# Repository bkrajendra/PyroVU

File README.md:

# PyroVU - Universal temperature sensor interface board

PyroVU is an universal temperature sensor module interface board for Sonpakhru board

## User Interface

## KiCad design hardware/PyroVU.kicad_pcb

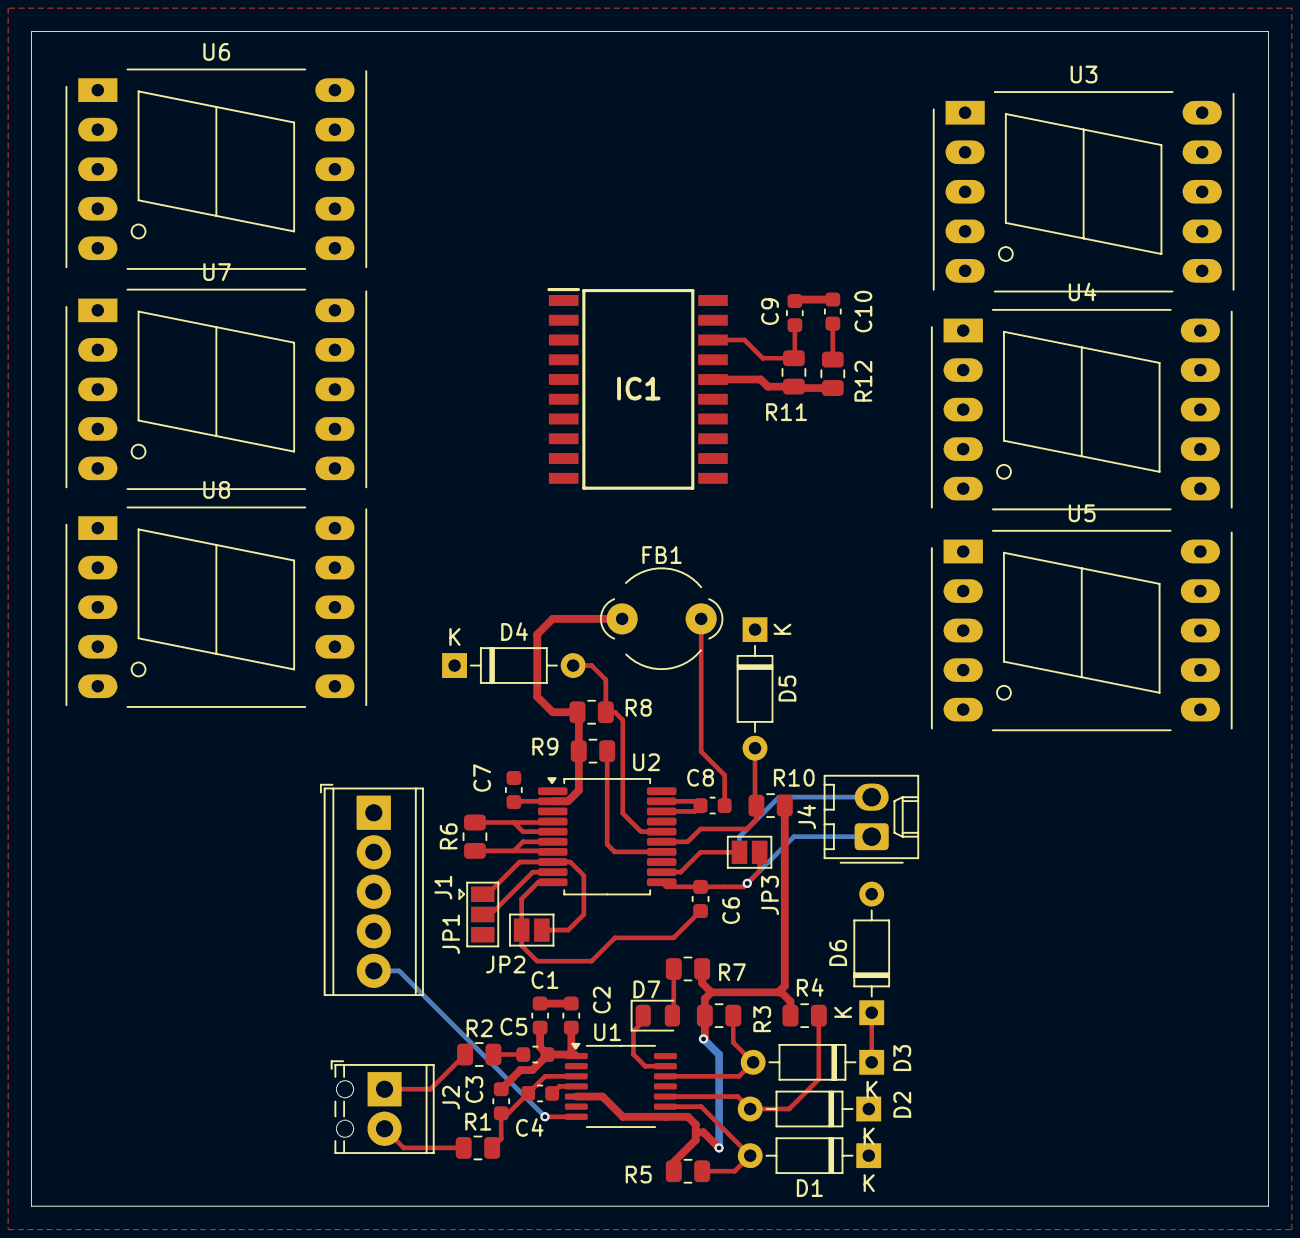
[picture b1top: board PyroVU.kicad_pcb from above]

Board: 2 copper layers, 79.5 x 75.5 mm, 45 parts (0 on the bottom side), 42 nets.

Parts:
C1, C2, C3, C4, C5, C7, C8: 0.1uF; C_0603_1608Metric
C6: 100nF; C_0603_1608Metric
C9, C10: 100pF; C_0603_1608Metric
D1, D2, D3, D4, D5, D6: 1N4148; D_DO-35_SOD27_P7.62mm_Horizontal
D7: LED; LED_0805_2012Metric
FB1: FerriteBead; LairdTech_28C0236-0JW-10
IC1: TM1637__SOP_; SOIC127P1045X280-20N
J1: Screw_Terminal_01x05; TerminalBlock_Phoenix_MPT-0,5-5-2.54_1x05_P2.54mm_Horizontal
J2: Screw_Terminal_01x02; TerminalBlock_Phoenix_MPT-0,5-2-2.54_1x02_P2.54mm_Horizontal
J4: Conn_01x02_Pin; Molex_KK-254_AE-6410-02A_1x02_P2.54mm_Vertical
JP1: SolderJumper_3_Open; SolderJumper-3_P1.3mm_Open_Pad1.0x1.5mm
JP2, JP3: SolderJumper_2_Open; SolderJumper-2_P1.3mm_Open_Pad1.0x1.5mm
R1, R2: 100; R_0805_2012Metric
R3, R4, R5, R8, R9, R10, R11, R12: 10k; R_0805_2012Metric
R6: 400; R_0805_2012Metric
R7: 330; R_0805_2012Metric
U1: MAX31856; TSSOP-14_4.4x5mm_P0.65mm
U2: MAX31865xAP; SSOP-20_5.3x7.2mm_P0.65mm
U3, U4, U5, U6, U7, U8: SM420561N; 7SegmentLED_LTS6760_LTS6780

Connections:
+3.3V: C1.2, C2.1, C7.2, FB1.1, IC1.16 (VDD), R3.1, R4.1, R5.1, R7.1, R8.1, R9.1, R10.1, R11.2, R12.2, U1.5 (AVDD), U1.8 (DVDD), U2.2 (DVDD)
/CLK: C9.2, IC1.18 (CLK), R11.1
/DIO: C10.2, IC1.17 (DIO), R12.1
/DRDY: J1.5, U1.7 (~DRDY), U2.1 (~DRDY)
/FAULT: D7.1 (K), U1.13 (~FAULT)
/GRID1: IC1.15 (GRID1), U5.3 (CC), U5.8 (CC)
/GRID2: IC1.14 (GRID2), U4.3 (CC), U4.8 (CC)
/GRID3: IC1.13 (GRID3), U3.3 (CC), U3.8 (CC)
/GRID4: IC1.12 (GRID4), U6.3 (CC), U6.8 (CC)
/GRID5: IC1.11 (GRID5), U7.3 (CC), U7.8 (CC)
/GRID6: IC1.10 (GRID6), U8.3 (CC), U8.8 (CC)
/SCLK: D5.1 (K), J1.1
/SDI: D3.1 (K), D6.1 (K), J1.3
/SDO: J1.2, U1.11 (SDO), U2.17 (SDO)
/SEG1: IC1.2 (SEG1/KS1), U3.7 (A), U4.7 (A), U5.7 (A), U6.7 (A), U7.7 (A), U8.7 (A)
/SEG2: IC1.3 (SEG2/KS2), U3.6 (B), U4.6 (B), U5.6 (B), U6.6 (B), U7.6 (B), U8.6 (B)
/SEG3: IC1.4 (SEG3/KS3), U3.4 (C), U4.4 (C), U5.4 (C), U6.4 (C), U7.4 (C), U8.4 (C)
/SEG4: IC1.5 (SEG4/KS4), U3.2 (D), U4.2 (D), U5.2 (D), U6.2 (D), U7.2 (D), U8.2 (D)
/SEG5: IC1.6 (SEG5/KS5), U3.1 (E), U4.1 (E), U5.1 (E), U6.1 (E), U7.1 (E), U8.1 (E)
/SEG6: IC1.7 (SEG6/KS6), U3.9 (F), U4.9 (F), U5.9 (F), U6.9 (F), U7.9 (F), U8.9 (F)
/SEG7: IC1.8 (SEG7/KS7), U3.10 (G), U4.10 (G), U5.10 (G), U6.10 (G), U7.10 (G), U8.10 (G)
/SEG8: IC1.9 (SEG8/KS8), U3.5 (DP), U4.5 (DP), U5.5 (DP), U6.5 (DP), U7.5 (DP), U8.5 (DP)
GND: C1.1, C2.2, C3.1, C5.2, C7.1, C8.1, C9.1, C10.1, IC1.1 (GND), JP1.3 (B), U1.1 (AGND), U1.14 (DGND), U2.13 (GND), U2.18 (DGND), U2.19 (GND)
unnamed: D1.2 (A), R5.2, U1.9 (~CS)
unnamed: D2.2 (A), R4.2, U1.10 (SCK)
unnamed: D3.2 (A), R3.2, U1.12 (SDI)
unnamed: D4.2 (A), R8.2, U2.16 (~CS)
unnamed: D5.2 (A), R10.2, U2.15 (SCLK)
unnamed: D6.2 (A), R9.2, U2.14 (SDI)
unnamed: D7.2 (A), R7.2
unnamed: J2.1, R2.1
unnamed: J2.2, R1.1, U1.2 (BIAS)
unnamed: JP1.1 (A), JP2.2 (B), U2.8 (FORCE+)
unnamed: C6.1, JP2.1 (A), U2.10 (RTDIN+)
unnamed: C6.2, J4.1, JP3.2 (B), U2.11 (RTDIN-)
unnamed: J4.2, JP3.1 (A), U2.12 (FORCE-)
unnamed: JP1.2 (C), U2.9 (FORCE2)
unnamed: C4.2, C5.1, R2.2, U1.4 (T+)
unnamed: C3.2, C4.1, R1.2, U1.3 (T-)
unnamed: R6.2, U2.4 (BIAS), U2.5 (REFIN+)
unnamed: R6.1, U2.6 (REFIN-), U2.7 (ISENSOR)
unnamed: C8.2, FB1.2, U2.3 (VDD)

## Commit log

2024-07-20 Fix: added gitignore
2024-07-21 Fix: library updates
2024-07-21 Fix: updated name
2024-07-21 Fix: updated readme
2024-07-23 Added the word file with few details
2024-07-28 Added: Updated code with class for data collection
2024-07-29 Updated schematic added footprints and edited doc file
2024-08-01 Added the new LED driver
2024-08-04 Assigned the footprints
2024-08-06 Updated the schematic and added 7seg display
2024-08-08 Changes in the Schematic
2024-08-09 Added tm1637 display option
